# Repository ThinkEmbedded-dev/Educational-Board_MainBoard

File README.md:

# ThinkEmbeded Base Sensor Board
The ThinkEmbeded Base Sensor Board is a versatile sensor board designed for various embedded applications. 
It features multiple sensors, including temperature, humidity, light, accelerometer, and more, making it ideal for IoT projects, environmental monitoring, and data logging.

## Features
- Multiple integrated sensors (temperature, humidity, light, accelerometer, etc.)
- Compact and lightweight design
- Easy to interface with Nucleo boards
- Supports I2C and SPI external connections
- Onboard power regulation
- Extended by additional sheild for IoT connectivity and AI capabilities

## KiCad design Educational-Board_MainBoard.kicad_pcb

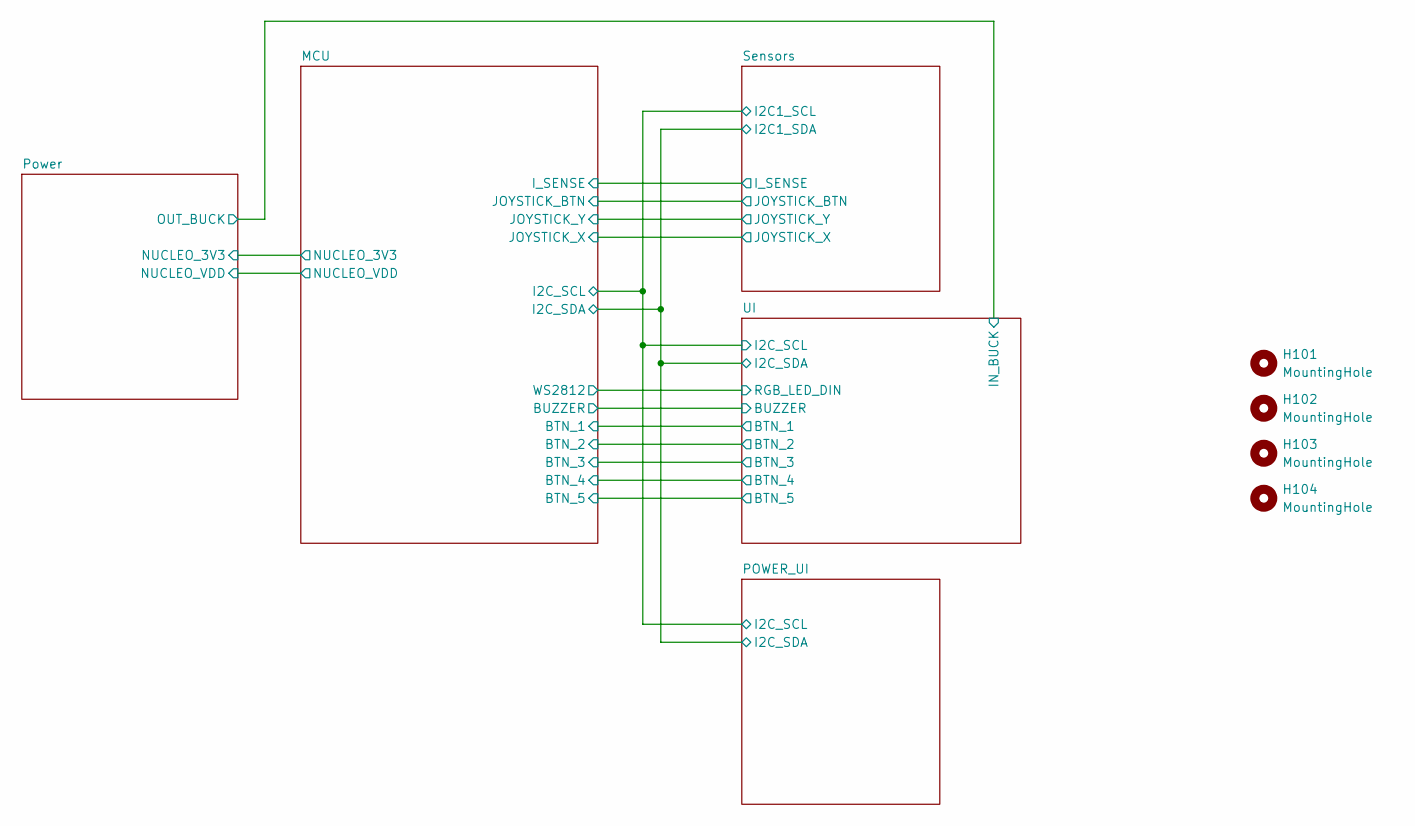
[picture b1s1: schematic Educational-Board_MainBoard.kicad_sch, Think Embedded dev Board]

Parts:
H101, H102, H103, H104: MountingHole; MountingHole_3.2mm_M3_ISO14580

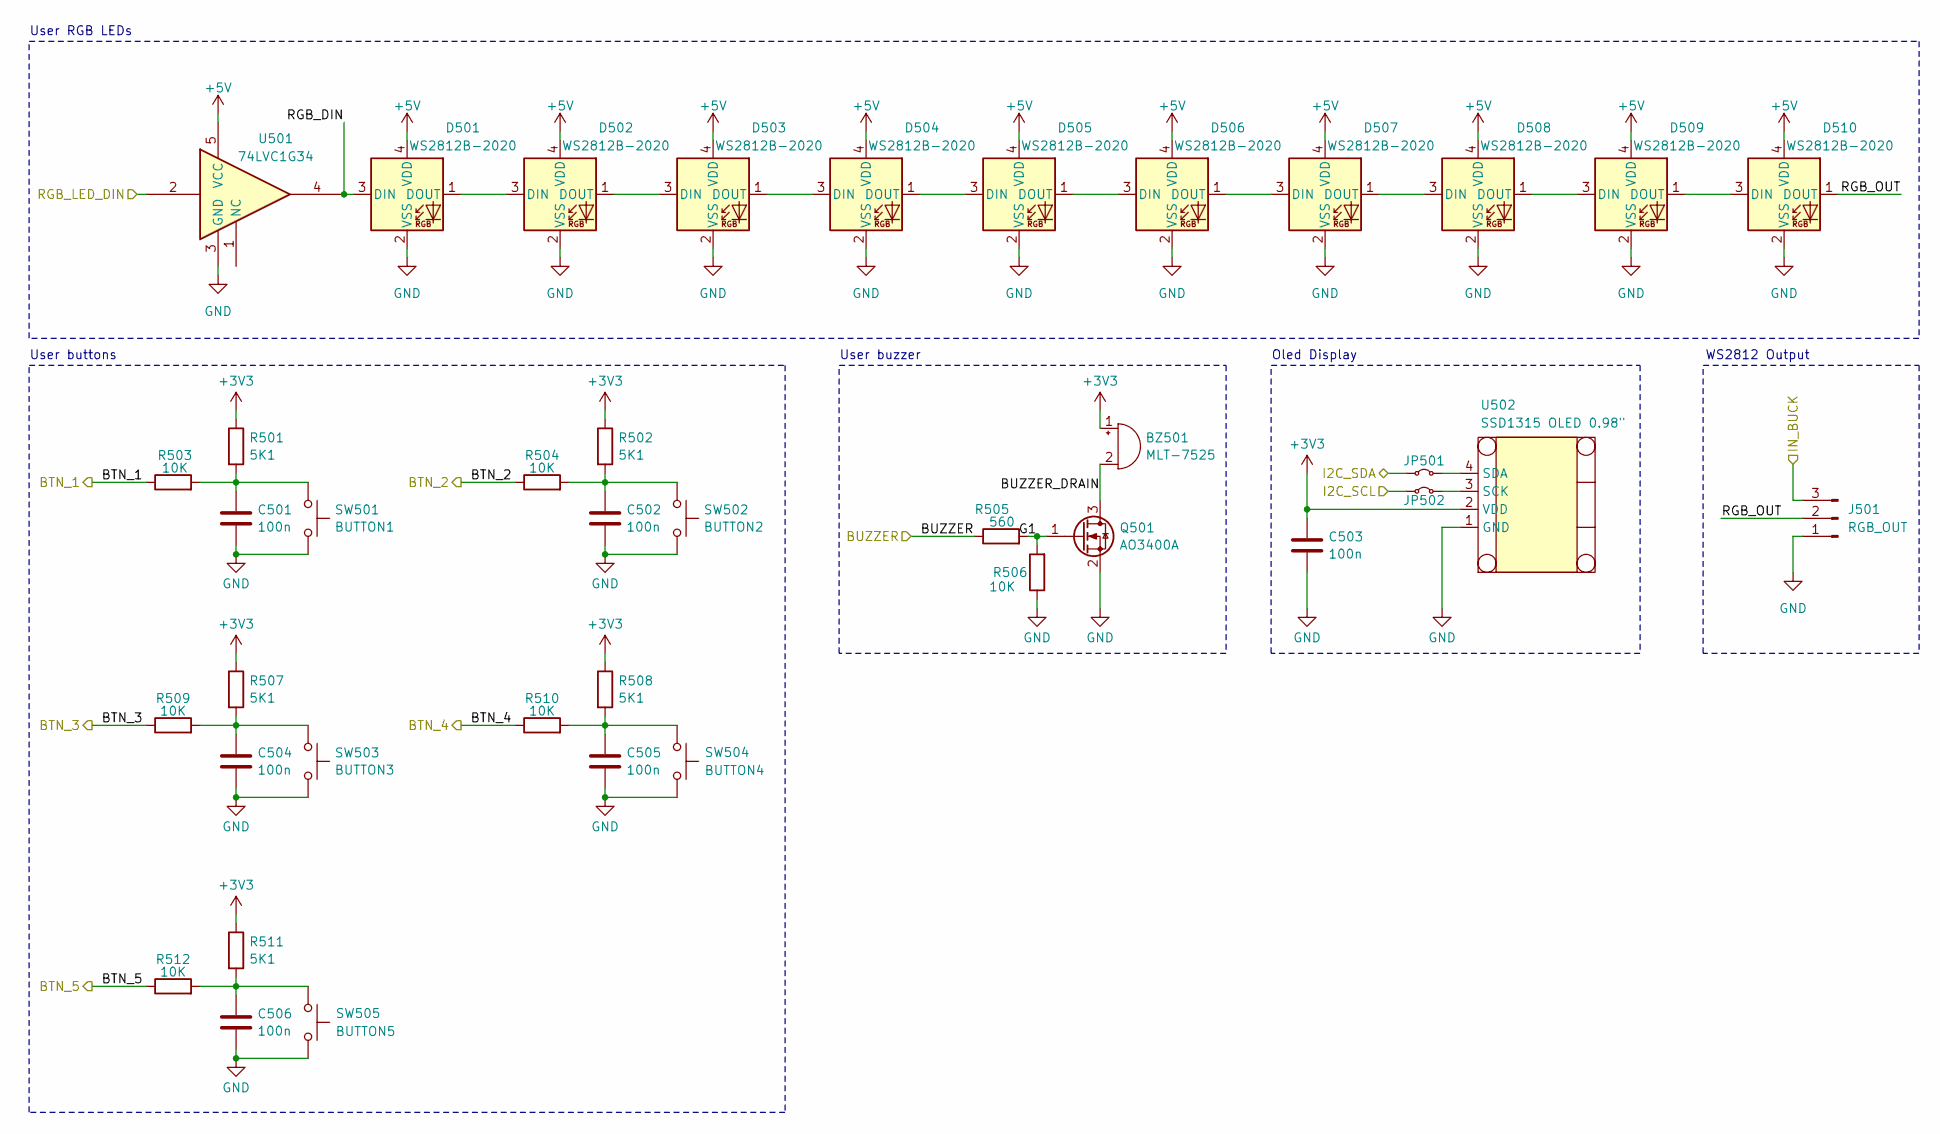
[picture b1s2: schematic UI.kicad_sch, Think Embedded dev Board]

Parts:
BZ501: MLT-7525; MLT-8530; LCSC C95299
C501, C502, C503, C504, C505, C506: 100n; C_0603_1608Metric_Pad1.08x0.95mm_HandSolder; LCSC C14663
D501, D502, D503, D504, D505, D506, D507, D508, D509, D510: WS2812B-2020; LED_WS2812B-2020_PLCC4_2.0x2.0mm; LCSC C965555
J501: RGB_OUT; PinHeader_1x03_P2.54mm_Vertical; LCSC C492402
JP501, JP502: 0R; R_0603_1608Metric_Pad0.98x0.95mm_HandSolder; LCSC C21189
Q501: AO3400A; SOT-23; LCSC C5380685
R501, R502, R507, R508, R511: 5K1; R_0603_1608Metric_Pad0.98x0.95mm_HandSolder; LCSC C23186
R503, R504, R506, R509, R510, R512: 10K; R_0603_1608Metric_Pad0.98x0.95mm_HandSolder; LCSC C25804
R505: 560; R_0603_1608Metric_Pad0.98x0.95mm_HandSolder; LCSC C23204
SW501: BUTTON1; SW_Push_1P1T_NO_CK_PTS125Sx43SMTR; LCSC C455223
SW502: BUTTON2; SW_Push_1P1T_NO_CK_PTS125Sx43SMTR; LCSC C455223
SW503: BUTTON3; SW_Push_1P1T_NO_CK_PTS125Sx43SMTR; LCSC C455223
SW504: BUTTON4; SW_Push_1P1T_NO_CK_PTS125Sx43SMTR; LCSC C455223
SW505: BUTTON5; SW_Push_1P1T_NO_CK_PTS125Sx43SMTR; LCSC C455223
U501: 74LVC1G34; SOT-23-5; LCSC C42380693
U502: SSD1315 OLED 0.98"; SSD1306; LCSC C5248080

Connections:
+3V3: BZ501.1 (+), C503.1, R501.1, R502.1, R507.1, R508.1, R511.1, U502.2 (VDD); also elsewhere on the board
+5V: D501.4 (VDD), D502.4 (VDD), D503.4 (VDD), D504.4 (VDD), D505.4 (VDD), D506.4 (VDD), D507.4 (VDD), D508.4 (VDD), D509.4 (VDD), D510.4 (VDD), U501.5 (VCC); also elsewhere on the board
/MCU/BTN_1: R503.1; also elsewhere on the board
/MCU/BTN_2: R504.1; also elsewhere on the board
/MCU/BTN_3: R509.1; also elsewhere on the board
/MCU/BTN_4: R510.1; also elsewhere on the board
/MCU/BTN_5: R512.1; also elsewhere on the board
/MCU/I2C_SCL: JP502.1 (A); also elsewhere on the board
/MCU/I2C_SDA: JP501.1 (A); also elsewhere on the board
/MCU/WS2812: U501.2; also elsewhere on the board
/Power/OUT_BUCK: J501.3; also elsewhere on the board
/UI/BUZZER: R505.1; also elsewhere on the board
/UI/BUZZER_DRAIN: BZ501.2 (-), Q501.3 (D)
/UI/G1: Q501.1 (G), R505.2, R506.2
/UI/RGB_DIN: D501.3 (DIN), U501.4
/UI/RGB_OUT: D510.1 (DOUT), J501.2
GND: C501.2, C502.2, C503.2, C504.2, C505.2, C506.2, D501.2 (VSS), D502.2 (VSS), D503.2 (VSS), D504.2 (VSS), D505.2 (VSS), D506.2 (VSS), D507.2 (VSS), D508.2 (VSS), D509.2 (VSS), D510.2 (VSS), J501.1, Q501.2 (S), R506.1, SW501.2, SW502.2, SW503.2, SW504.2, SW505.2, U501.3 (GND), U502.1 (GND); also elsewhere on the board
unnamed: C501.1, R501.2, R503.2, SW501.1
unnamed: C502.1, R502.2, R504.2, SW502.1
unnamed: C504.1, R507.2, R509.2, SW503.1
unnamed: C505.1, R508.2, R510.2, SW504.1
unnamed: C506.1, R511.2, R512.2, SW505.1
unnamed: D501.1 (DOUT), D502.3 (DIN)
unnamed: D502.1 (DOUT), D503.3 (DIN)
unnamed: D503.1 (DOUT), D504.3 (DIN)
unnamed: D504.1 (DOUT), D505.3 (DIN)
unnamed: D505.1 (DOUT), D506.3 (DIN)
unnamed: D506.1 (DOUT), D507.3 (DIN)
unnamed: D507.1 (DOUT), D508.3 (DIN)
unnamed: D508.1 (DOUT), D509.3 (DIN)
unnamed: D509.1 (DOUT), D510.3 (DIN)
unnamed: JP501.2 (B), U502.4 (SDA)
unnamed: JP502.2 (B), U502.3 (SCK)

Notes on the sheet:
WS2812 Output
Oled Display
User RGB LEDs
User buzzer
User buttons

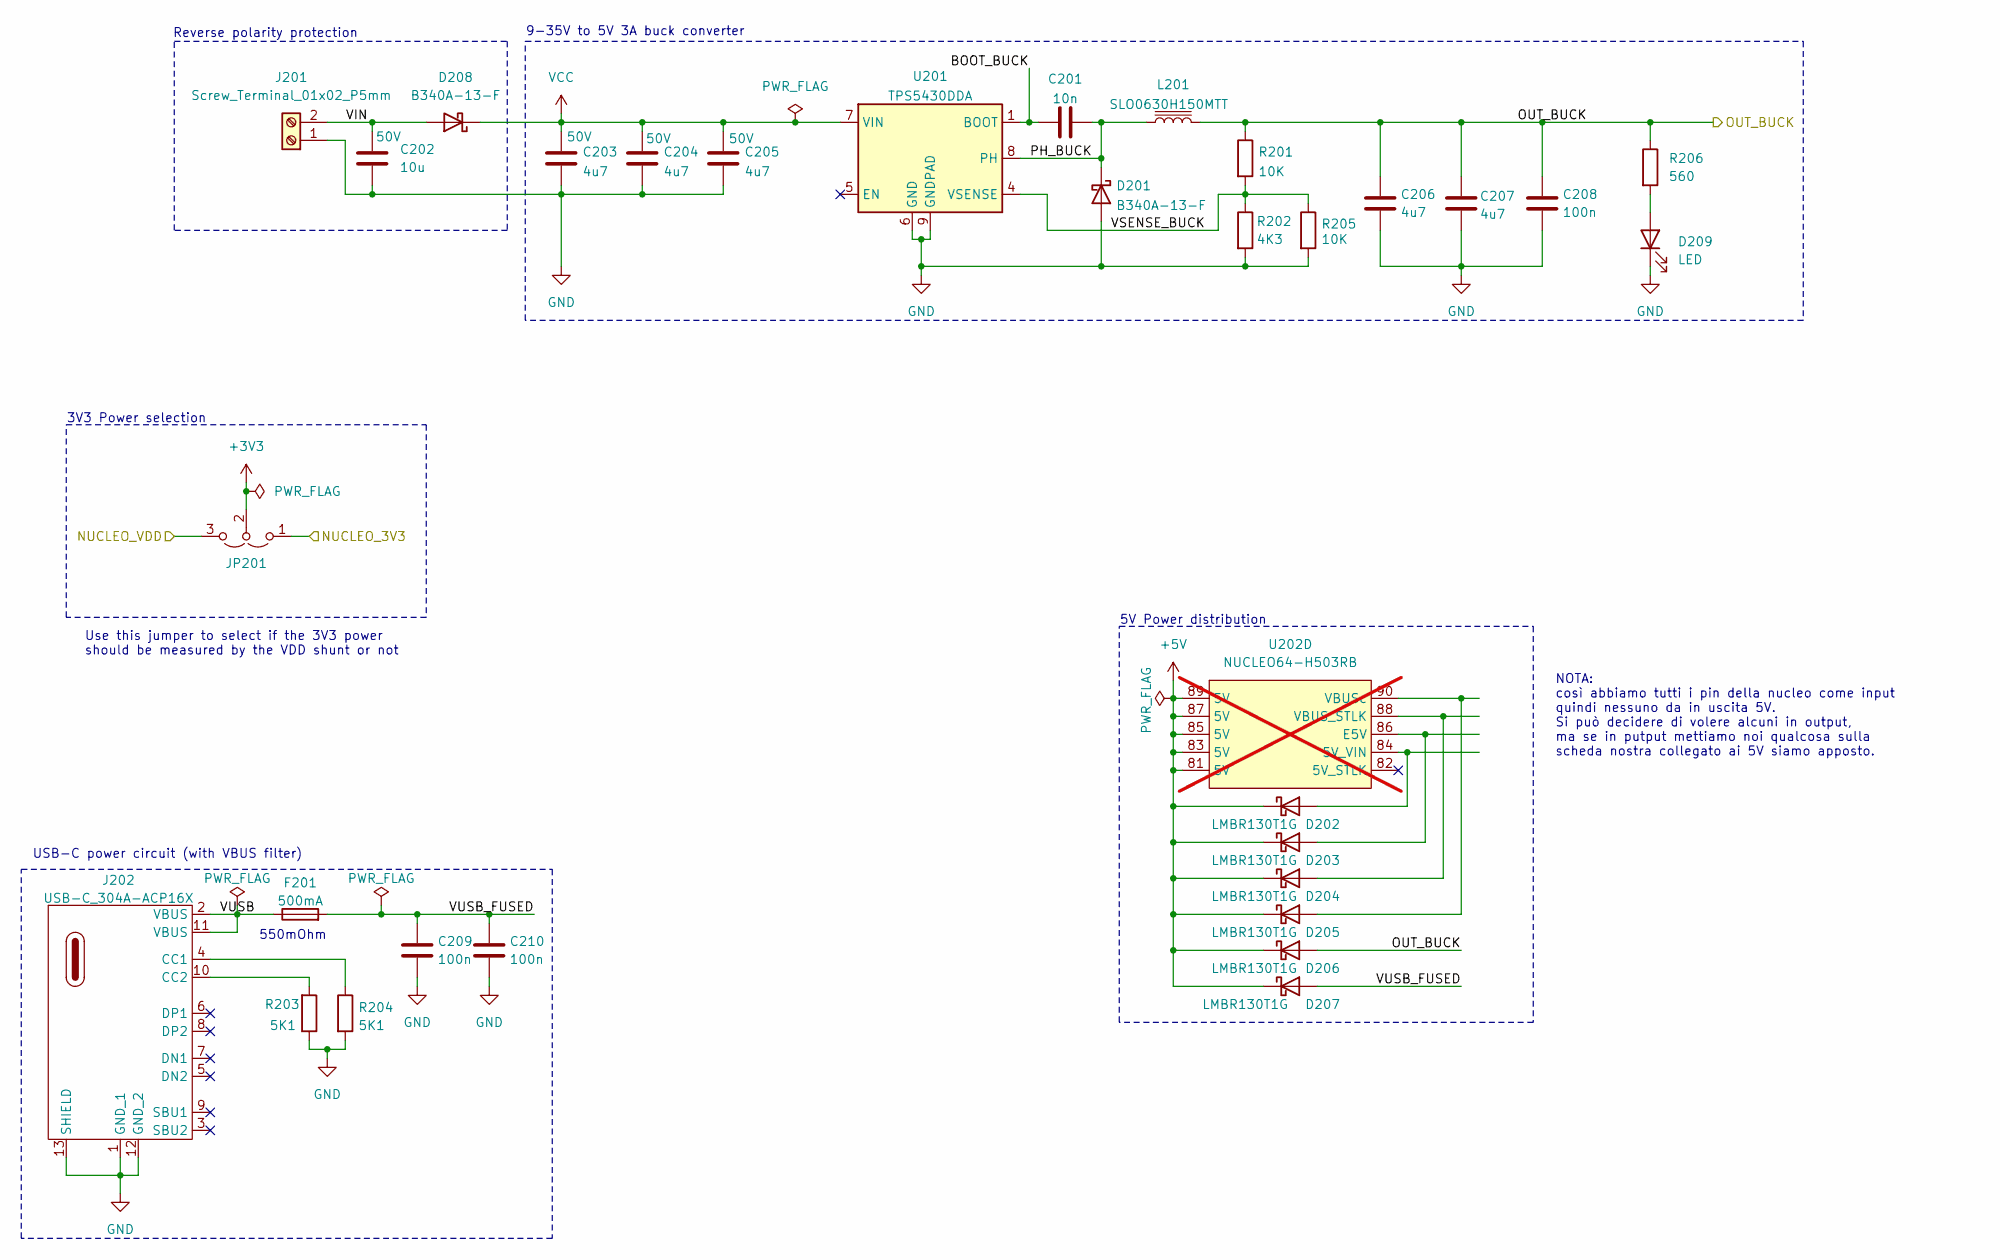
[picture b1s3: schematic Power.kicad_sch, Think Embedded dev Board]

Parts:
C201: 10n; C_0603_1608Metric_Pad1.08x0.95mm_HandSolder; LCSC C57112
C202: 10u; C_0603_1608Metric_Pad1.08x0.95mm_HandSolder; Voltage 50V; LCSC C19702
C203, C204, C205: 4u7; C_0603_1608Metric_Pad1.08x0.95mm_HandSolder; Voltage 50V; LCSC C19666
C206, C207: 4u7; C_0603_1608Metric_Pad1.08x0.95mm_HandSolder; LCSC C19666
C208, C209, C210: 100n; C_0603_1608Metric_Pad1.08x0.95mm_HandSolder; LCSC C14663
D201, D208: B340A-13-F; D_SMA; LCSC C85098
D202, D203, D204, D205, D206, D207: LMBR130T1G; D_SOD-123; LCSC C48974
D209: LED; LED_0603_1608Metric; LCSC C2290
F201: 500mA; Fuse_1206_3216Metric_Pad1.42x1.75mm_HandSolder; LCSC C151133
J201: Screw_Terminal_01x02_P5mm; TerminalBlock_MaiXu_MX126-5.0-02P_1x02_P5.00mm; LCSC C474881
J202: USB-C_304A-ACP16X; USB_C_304A-ACP16X; LCSC C2909610
JP201: Jumper_3_Open; PinHeader_1x03_P2.54mm_Vertical; LCSC C492402
L201: SLO0630H150MTT; L_AVX_LMLP07A7; LCSC C182182
R201, R205: 10K; R_0603_1608Metric_Pad0.98x0.95mm_HandSolder; LCSC C25804
R202: 4K3; R_0603_1608Metric_Pad0.98x0.95mm_HandSolder; LCSC C23159
R203, R204: 5K1; R_0603_1608Metric_Pad0.98x0.95mm_HandSolder; LCSC C23186
R206: 560; R_0603_1608Metric_Pad0.98x0.95mm_HandSolder; LCSC C23204
U201: TPS5430DDA; TI_SO-PowerPAD-8_ThermalVias; LCSC C9864
U202: NUCLEO64-H503RB; Nucleo64_ST-Morpho; not fitted

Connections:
+3V3: JP201.2 (C); also elsewhere on the board
+5V: D202.1 (K), D203.1 (K), D204.1 (K), D205.1 (K), D206.1 (K), D207.1 (K), U202.81 (5V), U202.83 (5V), U202.85 (5V), U202.87 (5V), U202.89 (5V); also elsewhere on the board
/MCU/NUCLEO_3V3: JP201.1 (A); also elsewhere on the board
/MCU/NUCLEO_VDD: JP201.3 (B); also elsewhere on the board
/Power/BOOT_BUCK: C201.1, U201.1 (BOOT)
/Power/OUT_BUCK: C206.1, C207.1, C208.1, D206.2 (A), L201.2, R201.1, R206.1; also elsewhere on the board
/Power/PH_BUCK: C201.2, D201.1 (K), L201.1, U201.8 (PH)
/Power/VIN: C202.1, D208.2 (A), J201.2
/Power/VSENSE_BUCK: R201.2, R202.1, R205.1, U201.4 (VSENSE)
/Power/VUSB: F201.1, J202.2 (VBUS), J202.11 (VBUS)
/Power/VUSB_FUSED: C209.1, C210.1, D207.2 (A), F201.2
GND: C202.2, C203.2, C204.2, C205.2, C206.2, C207.2, C208.2, C209.2, C210.2, D201.2 (A), D209.1 (K), J201.1, J202.1 (GND_1), J202.12 (GND_2), J202.13 (SHIELD), R202.2, R203.1, R204.2, R205.2, U201.6 (GND), U201.9 (GNDPAD); also elsewhere on the board
unnamed: D202.2 (A), U202.84 (5V_VIN)
unnamed: D203.2 (A), U202.86 (E5V)
unnamed: D204.2 (A), U202.88 (VBUS_STLK)
unnamed: D205.2 (A), U202.90 (VBUSc)
unnamed: D209.2 (A), R206.2
unnamed: J202.4 (CC1), R204.1
unnamed: J202.10 (CC2), R203.2
VCC: C203.1, C204.1, C205.1, D208.1 (K), U201.7 (VIN)

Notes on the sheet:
Use this jumper to select if the 3V3 power should be measured by the VDD shunt or not
5V Power distribution
550mOhm
9-35V to 5V 3A buck converter
Reverse polarity protection
USB-C power circuit (with VBUS filter)
3V3 Power selection
NOTA: così abbiamo tutti i pin della nucleo come input quindi nessuno da in uscita 5V. Si può decidere di volere alcuni in output, ma se in putput mettiamo noi qualcosa sulla scheda nostra collegato ai 5V siamo apposto.

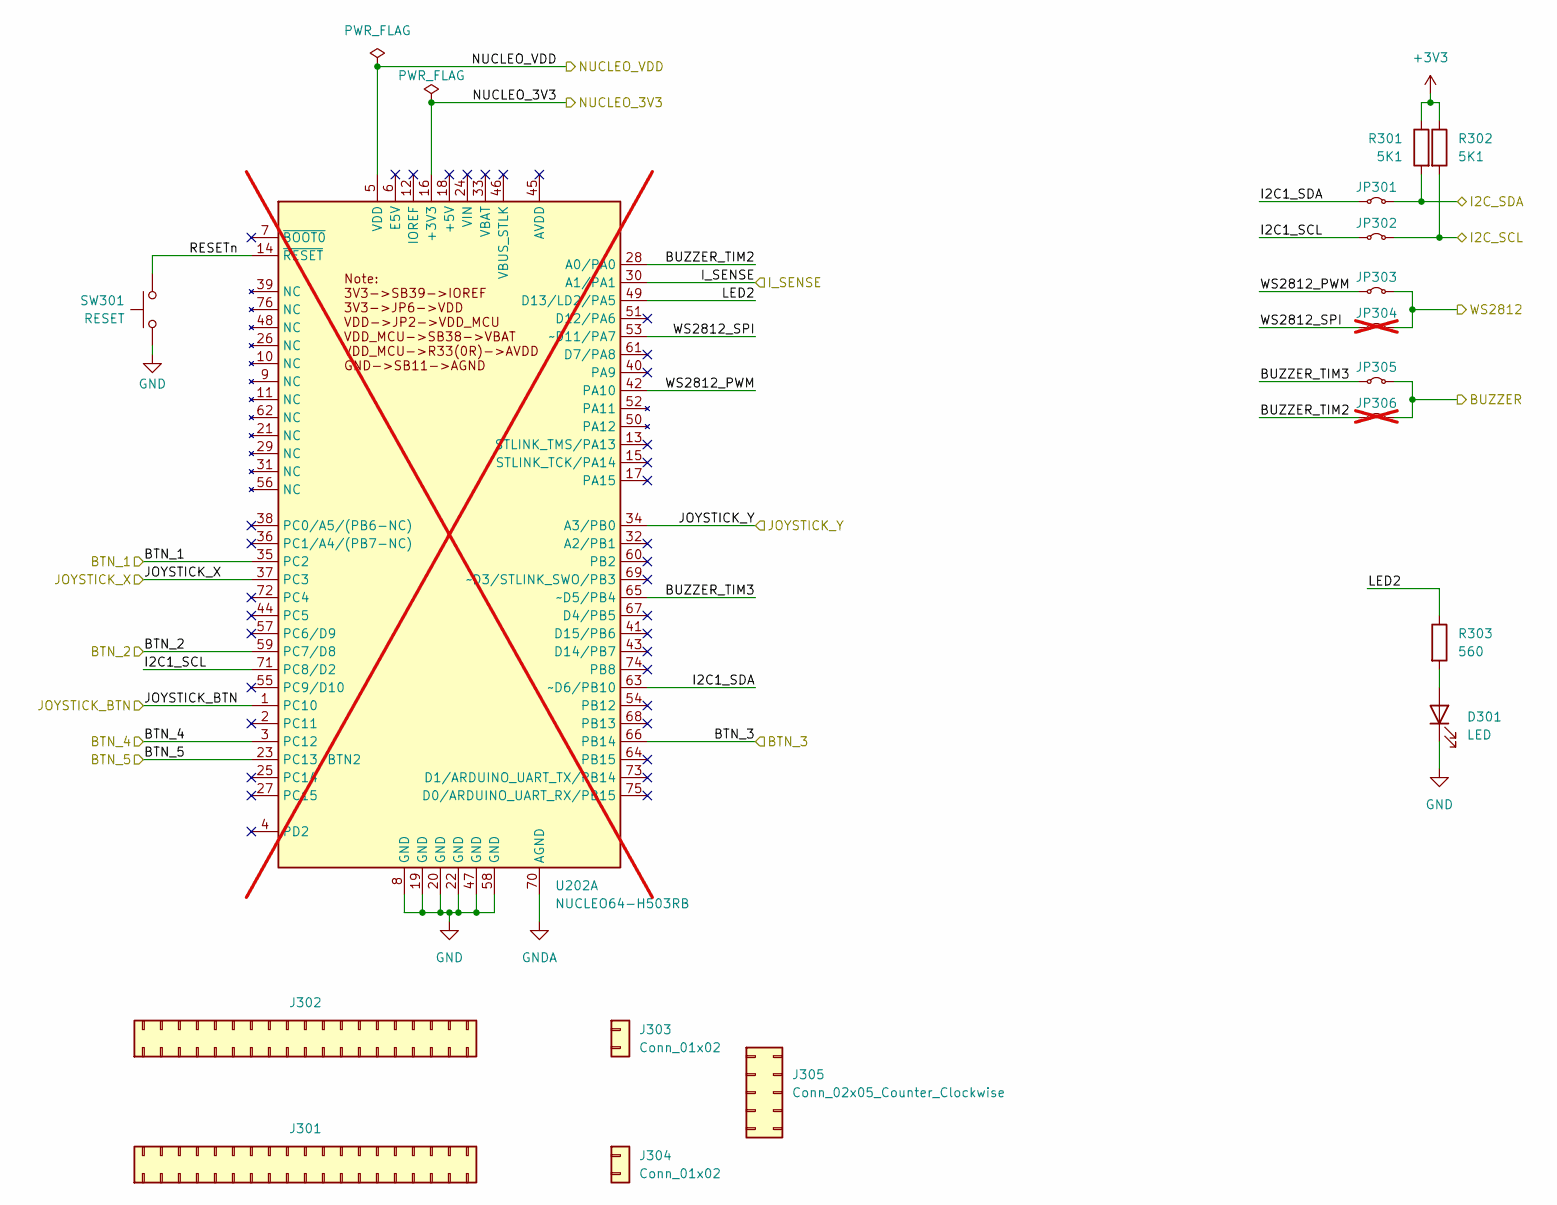
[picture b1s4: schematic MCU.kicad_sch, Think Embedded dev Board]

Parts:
D301: LED; LED_0603_1608Metric; LCSC C2290
J301, J302: Conn_02x20_Counter_Clockwise; PLACEHOLDER_PinSocket_2x19_P2.54mm_Vertical; LCSC C2977589
J303, J304: Conn_01x02; PLACEHOLDER_PinSocket_1x02_P2.54mm_Vertical; LCSC C492401
J305: Conn_02x05_Counter_Clockwise; PLACEHOLDER_PinSocket_2x05_P2.54mm_Vertical; LCSC C92270
JP301, JP302, JP303, JP305: 0R; R_0603_1608Metric_Pad0.98x0.95mm_HandSolder; LCSC C21189
JP304, JP306: 0R; R_0603_1608Metric_Pad0.98x0.95mm_HandSolder; LCSC C21189; not fitted
R301, R302: 5K1; R_0603_1608Metric_Pad0.98x0.95mm_HandSolder; LCSC C23186
R303: 560; R_0603_1608Metric_Pad0.98x0.95mm_HandSolder; LCSC C23204
SW301: RESET; SW_SPST_SKQG_WithoutStem; LCSC C455108
U202: NUCLEO64-H503RB; Nucleo64; not fitted

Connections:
+3V3: R301.1, R302.1; also elsewhere on the board
/MCU/BTN_1: U202.35 (PC2); also elsewhere on the board
/MCU/BTN_2: U202.59 (PC7); also elsewhere on the board
/MCU/BTN_3: U202.66 (PB14); also elsewhere on the board
/MCU/BTN_4: U202.3 (PC12); also elsewhere on the board
/MCU/BTN_5: U202.23 (PC13/BTN2); also elsewhere on the board
/MCU/BUZZER_TIM2: JP306.1 (A), U202.28 (PA0)
/MCU/BUZZER_TIM3: JP305.1 (A), U202.65 (PB4)
/MCU/I2C1_SCL: JP302.1 (A), U202.71 (PC8)
/MCU/I2C1_SDA: JP301.1 (A), U202.63 (PB10)
/MCU/I2C_SCL: JP302.2 (B), R302.2; also elsewhere on the board
/MCU/I2C_SDA: JP301.2 (B), R301.2; also elsewhere on the board
/MCU/I_SENSE: U202.30 (PA1); also elsewhere on the board
/MCU/JOYSTICK_BTN: U202.1 (PC10); also elsewhere on the board
/MCU/JOYSTICK_X: U202.37 (PC3); also elsewhere on the board
/MCU/JOYSTICK_Y: U202.34 (PB0); also elsewhere on the board
/MCU/LED2: R303.1, U202.49 (LD2/PA5)
/MCU/NUCLEO_3V3: U202.16 (+3V3); also elsewhere on the board
/MCU/NUCLEO_VDD: U202.5 (VDD); also elsewhere on the board
/MCU/RESETn: SW301.1, U202.14 (~RESET)
/MCU/WS2812: JP303.2 (B), JP304.2 (B); also elsewhere on the board
/MCU/WS2812_PWM: JP303.1 (A), U202.42 (PA10)
/MCU/WS2812_SPI: JP304.1 (A), U202.53 (PA7)
/UI/BUZZER: JP305.2 (B), JP306.2 (B); also elsewhere on the board
GND: D301.1 (K), SW301.2, U202.8 (GND), U202.19 (GND), U202.20 (GND), U202.22 (GND), U202.47 (GND), U202.58 (GND); also elsewhere on the board
GNDA: U202.70 (AGND)
unnamed: D301.2 (A), R303.2

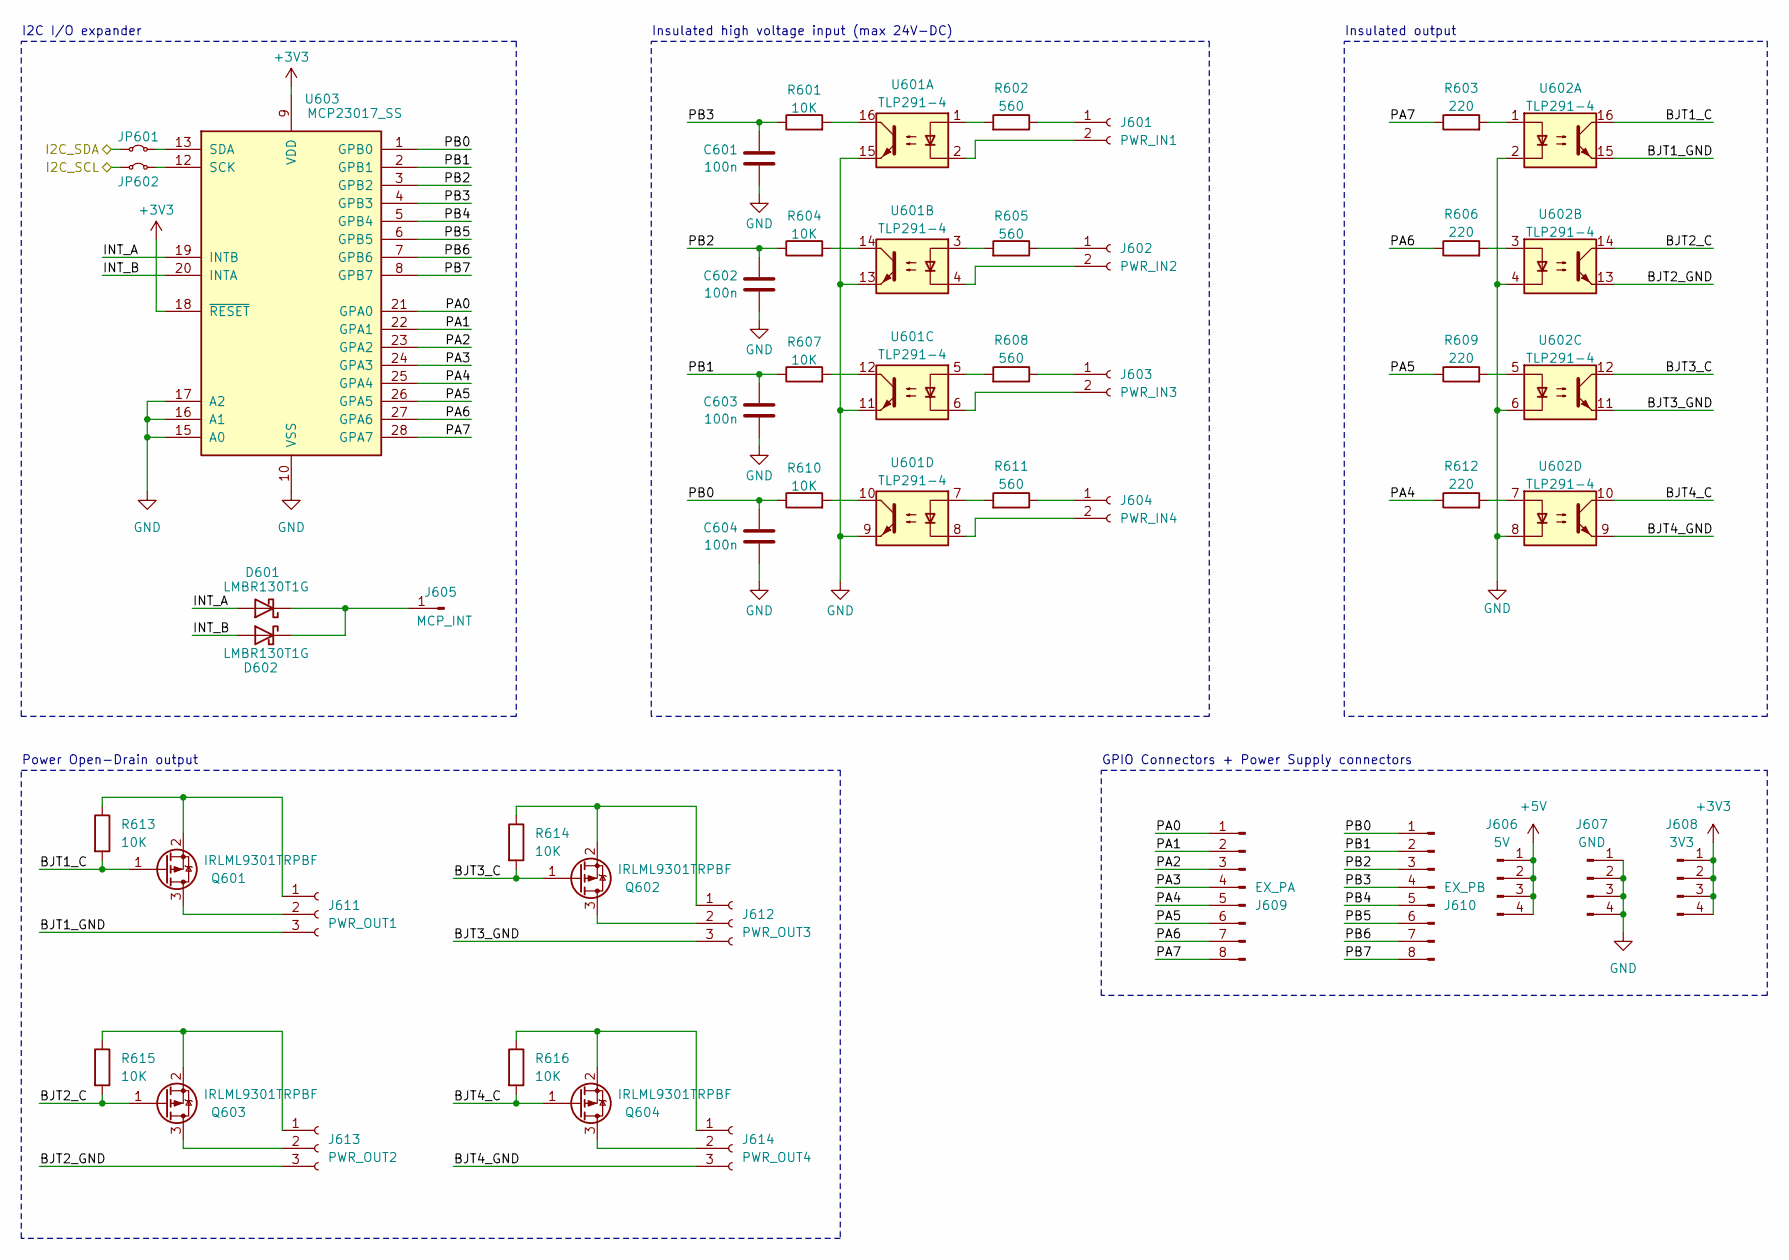
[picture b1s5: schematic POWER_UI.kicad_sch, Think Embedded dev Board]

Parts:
C601, C602, C603, C604: 100n; C_0603_1608Metric_Pad1.08x0.95mm_HandSolder; LCSC C14663
D601, D602: LMBR130T1G; D_SOD-123; LCSC C48974
J601: PWR_IN1; PinHeader_1x02_P2.54mm_Vertical; LCSC C492401
J602: PWR_IN2; PinHeader_1x02_P2.54mm_Vertical; LCSC C492401
J603: PWR_IN3; PinHeader_1x02_P2.54mm_Vertical; LCSC C492401
J604: PWR_IN4; PinHeader_1x02_P2.54mm_Vertical; LCSC C492401
J605: MCP_INT; PinHeader_1x01_P2.54mm_Vertical; LCSC C492400
J606: 5V; PinHeader_1x04_P2.54mm_Vertical; LCSC C492403
J607: GND; PinHeader_1x04_P2.54mm_Vertical; LCSC C492403
J608: 3V3; PinHeader_1x04_P2.54mm_Vertical; LCSC C492403
J609: EX_PA; PinHeader_1x08_P2.54mm_Vertical; LCSC C492407
J610: EX_PB; PinHeader_1x08_P2.54mm_Vertical; LCSC C492407
J611: PWR_OUT1; PinHeader_1x03_P2.54mm_Vertical; LCSC C492402
J612: PWR_OUT3; PinHeader_1x03_P2.54mm_Vertical; LCSC C492402
J613: PWR_OUT2; PinHeader_1x03_P2.54mm_Vertical; LCSC C492402
J614: PWR_OUT4; PinHeader_1x03_P2.54mm_Vertical; LCSC C492402
JP601, JP602: 0R; R_0603_1608Metric_Pad0.98x0.95mm_HandSolder; LCSC C21189
Q601, Q602, Q603, Q604: IRLML9301TRPBF; SOT-23; LCSC C82056
R601, R604, R607, R610, R613, R614, R615, R616: 10K; R_0603_1608Metric_Pad0.98x0.95mm_HandSolder; LCSC C25804
R602, R605, R608, R611: 560; R_0603_1608Metric_Pad0.98x0.95mm_HandSolder; LCSC C23204
R603, R606, R609, R612: 220; R_0603_1608Metric_Pad0.98x0.95mm_HandSolder; LCSC C22962
U601, U602: TLP291-4; SOP-16_4.4x10.4mm_P1.27mm; LCSC C60900
U603: MCP23017_SS; SSOP-28_5.3x10.2mm_P0.65mm; LCSC C506653

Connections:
+3V3: J608.1, J608.2, J608.3, J608.4, U603.9 (VDD), U603.18 (~RESET); also elsewhere on the board
+5V: J606.1, J606.2, J606.3, J606.4; also elsewhere on the board
/MCU/I2C_SCL: JP602.1 (A); also elsewhere on the board
/MCU/I2C_SDA: JP601.1 (A); also elsewhere on the board
/POWER_UI/BJT1_C: Q601.1 (G), R613.2, U602.16
/POWER_UI/BJT1_GND: J611.3, U602.15
/POWER_UI/BJT2_C: Q603.1 (G), R615.2, U602.14
/POWER_UI/BJT2_GND: J613.3, U602.13
/POWER_UI/BJT3_C: Q602.1 (G), R614.2, U602.12
/POWER_UI/BJT3_GND: J612.3, U602.11
/POWER_UI/BJT4_C: Q604.1 (G), R616.2, U602.10
/POWER_UI/BJT4_GND: J614.3, U602.9
/POWER_UI/INT_A: D601.2 (A), U603.19 (INTB)
/POWER_UI/INT_B: D602.2 (A), U603.20 (INTA)
/POWER_UI/PA0: J609.1, U603.21 (GPA0)
/POWER_UI/PA1: J609.2, U603.22 (GPA1)
/POWER_UI/PA2: J609.3, U603.23 (GPA2)
/POWER_UI/PA3: J609.4, U603.24 (GPA3)
/POWER_UI/PA4: J609.5, R612.1, U603.25 (GPA4)
/POWER_UI/PA5: J609.6, R609.1, U603.26 (GPA5)
/POWER_UI/PA6: J609.7, R606.1, U603.27 (GPA6)
/POWER_UI/PA7: J609.8, R603.1, U603.28 (GPA7)
/POWER_UI/PB0: C604.1, J610.1, R610.1, U603.1 (GPB0)
/POWER_UI/PB1: C603.1, J610.2, R607.1, U603.2 (GPB1)
/POWER_UI/PB2: C602.1, J610.3, R604.1, U603.3 (GPB2)
/POWER_UI/PB3: C601.1, J610.4, R601.1, U603.4 (GPB3)
/POWER_UI/PB4: J610.5, U603.5 (GPB4)
/POWER_UI/PB5: J610.6, U603.6 (GPB5)
/POWER_UI/PB6: J610.7, U603.7 (GPB6)
/POWER_UI/PB7: J610.8, U603.8 (GPB7)
GND: C601.2, C602.2, C603.2, C604.2, J607.1, J607.2, J607.3, J607.4, U601.9, U601.11, U601.13, U601.15, U602.2, U602.4, U602.6, U602.8, U603.10 (VSS), U603.15 (A0), U603.16 (A1), U603.17 (A2); also elsewhere on the board
unnamed: D601.1 (K), D602.1 (K), J605.1
unnamed: J601.1, R602.1
unnamed: J601.2, U601.2
unnamed: J602.1, R605.1
unnamed: J602.2, U601.4
unnamed: J603.1, R608.1
unnamed: J603.2, U601.6
unnamed: J604.1, R611.1
unnamed: J604.2, U601.8
unnamed: J611.1, Q601.2 (S), R613.1
unnamed: J611.2, Q601.3 (D)
unnamed: J612.1, Q602.2 (S), R614.1
unnamed: J612.2, Q602.3 (D)
unnamed: J613.1, Q603.2 (S), R615.1
unnamed: J613.2, Q603.3 (D)
unnamed: J614.1, Q604.2 (S), R616.1
unnamed: J614.2, Q604.3 (D)
unnamed: JP601.2 (B), U603.13 (SDA)
unnamed: JP602.2 (B), U603.12 (SCK)
unnamed: R601.2, U601.16
unnamed: R602.2, U601.1
unnamed: R603.2, U602.1
unnamed: R604.2, U601.14
unnamed: R605.2, U601.3
unnamed: R606.2, U602.3
unnamed: R607.2, U601.12
unnamed: R608.2, U601.5
unnamed: R609.2, U602.5
unnamed: R610.2, U601.10
unnamed: R611.2, U601.7
unnamed: R612.2, U602.7

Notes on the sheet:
Insulated output
Insulated high voltage input (max 24V-DC)
I2C I/O expander
Power Open-Drain output
GPIO Connectors + Power Supply connectors

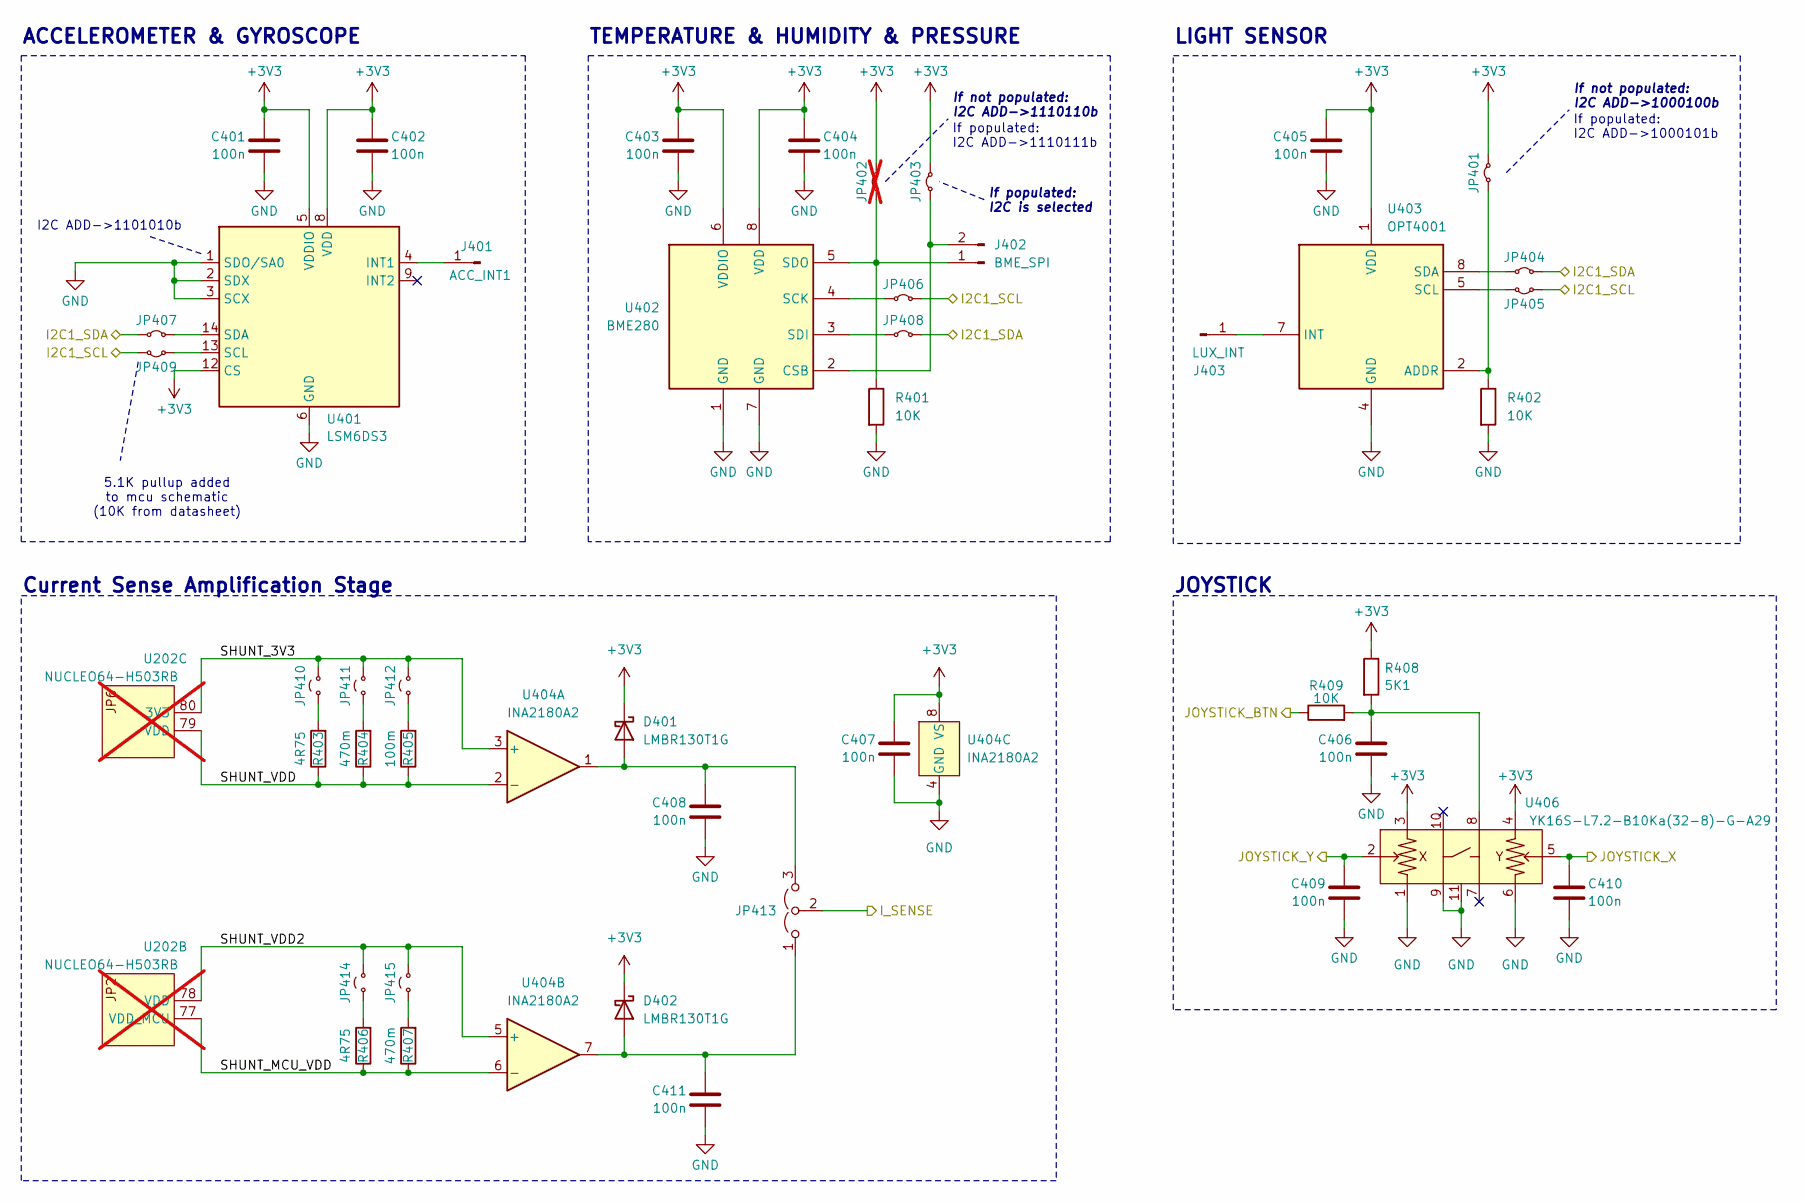
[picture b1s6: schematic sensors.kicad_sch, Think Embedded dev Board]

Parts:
C401, C402, C403, C404, C405, C406, C407, C408, C409, C410, C411: 100n; C_0603_1608Metric_Pad1.08x0.95mm_HandSolder; LCSC C14663
D401, D402: LMBR130T1G; D_SOD-123; LCSC C48974
J401: ACC_INT1; PinHeader_1x01_P2.54mm_Vertical; LCSC C492400
J402: BME_SPI; PinHeader_1x02_P2.54mm_Vertical; LCSC C492401
J403: LUX_INT; PinHeader_1x01_P2.54mm_Vertical; LCSC C492400
JP401, JP403, JP404, JP405, JP406, JP407, JP408, JP409: 0R; R_0603_1608Metric_Pad0.98x0.95mm_HandSolder; LCSC C21189
JP402: 0R; R_0603_1608Metric_Pad0.98x0.95mm_HandSolder; LCSC C21189; not fitted
JP410, JP411, JP412, JP414, JP415: Jumper_2_Small_Open; PinHeader_1x02_P2.54mm_Vertical; LCSC C492401
JP413: Jumper_3_Open; PinHeader_1x03_P2.54mm_Vertical; LCSC C492402
R401, R402, R409: 10K; R_0603_1608Metric_Pad0.98x0.95mm_HandSolder; LCSC C25804
R403, R406: 4R75; R_0603_1608Metric_Pad0.98x0.95mm_HandSolder; LCSC C2090841
R404, R407: 470m; R_0603_1608Metric_Pad0.98x0.95mm_HandSolder; LCSC C3013349
R405: 100m; R_0603_1608Metric_Pad0.98x0.95mm_HandSolder; LCSC C3013345
R408: 5K1; R_0603_1608Metric_Pad0.98x0.95mm_HandSolder; LCSC C23186
U202: NUCLEO64-H503RB; Nucleo64_ST-Morpho; not fitted
U401: LSM6DS3; LGA-14_3x2.5mm_P0.5mm_LayoutBorder3x4y; LCSC C967633
U402: BME280; Bosch_LGA-8_2.5x2.5mm_P0.65mm_ClockwisePinNumbering; LCSC C92489
U403: OPT4001; SOT-583-8; LCSC C17612395
U404: INA2180A2; VSSOP-8_3x3mm_P0.65mm; LCSC C2058508
U406: YK16S-L7.2-B10Ka(32-8)-G-A29; LCSC C37323746

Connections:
+3V3: C401.1, C402.1, C403.1, C404.1, C405.1, C407.1, D401.1 (K), D402.1 (K), JP401.2 (B), JP402.2 (B), JP403.2 (B), R408.1, U401.5 (VDDIO), U401.8 (VDD), U401.12 (CS), U402.6 (VDDIO), U402.8 (VDD), U403.1 (VDD), U404.8 (VS), U406.3, U406.4; also elsewhere on the board
/MCU/I2C_SCL: JP405.2 (B), JP406.2 (B), JP409.2 (B); also elsewhere on the board
/MCU/I2C_SDA: JP404.2 (B), JP407.1 (A), JP408.2 (B); also elsewhere on the board
/MCU/I_SENSE: JP413.2 (C); also elsewhere on the board
/MCU/JOYSTICK_BTN: R409.1; also elsewhere on the board
/MCU/JOYSTICK_X: C410.1, U406.5; also elsewhere on the board
/MCU/JOYSTICK_Y: C409.1, U406.2; also elsewhere on the board
/Sensors/SHUNT_3V3: JP410.2 (B), JP411.2 (B), JP412.2 (B), U202.80 (3V3), U404.3 (+)
/Sensors/SHUNT_MCU_VDD: R406.1, R407.1, U202.77 (VDD_MCU), U404.6 (-)
/Sensors/SHUNT_VDD: R403.1, R404.1, R405.1, U202.79 (VDD), U404.2 (-)
/Sensors/SHUNT_VDD2: JP414.2 (B), JP415.2 (B), U202.78 (VDD), U404.5 (+)
GND: C401.2, C402.2, C403.2, C404.2, C405.2, C406.2, C407.2, C408.2, C409.2, C410.2, C411.2, R401.2, R402.2, U401.1 (SDO/SA0), U401.2 (SDX), U401.3 (SCX), U401.6 (GND), U401.7 (GND), U402.1 (GND), U402.7 (GND), U403.4 (GND), U404.4 (GND), U406.1, U406.6, U406.9, U406.11; also elsewhere on the board
unnamed: C406.1, R408.2, R409.2, U406.8
unnamed: C408.1, D401.2 (A), JP413.3 (B), U404.1
unnamed: C411.1, D402.2 (A), JP413.1 (A), U404.7
unnamed: J401.1, U401.4 (INT1)
unnamed: J402.1, JP402.1 (A), R401.1, U402.5 (SDO)
unnamed: J402.2, JP403.1 (A), U402.2 (CSB)
unnamed: J403.1, U403.7 (INT)
unnamed: JP401.1 (A), R402.1, U403.2 (ADDR)
unnamed: JP404.1 (A), U403.8 (SDA)
unnamed: JP405.1 (A), U403.5 (SCL)
unnamed: JP406.1 (A), U402.4 (SCK)
unnamed: JP407.2 (B), U401.14 (SDA)
unnamed: JP408.1 (A), U402.3 (SDI)
unnamed: JP409.1 (A), U401.13 (SCL)
unnamed: JP410.1 (A), R403.2
unnamed: JP411.1 (A), R404.2
unnamed: JP412.1 (A), R405.2
unnamed: JP414.1 (A), R406.2
unnamed: JP415.1 (A), R407.2

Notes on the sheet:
Current Sense Amplification Stage
If populated: I2C ADD->1000101b
ACCELEROMETER & GYROSCOPE
If populated: I2C ADD->1110111b
5.1K pullup added to mcu schematic (10K from datasheet)
If not populated: I2C ADD->1110110b
TEMPERATURE & HUMIDITY & PRESSURE
LIGHT SENSOR
JOYSTICK
I2C ADD->1101010b
If not populated: I2C ADD->1000100b
If populated: I2C is selected
